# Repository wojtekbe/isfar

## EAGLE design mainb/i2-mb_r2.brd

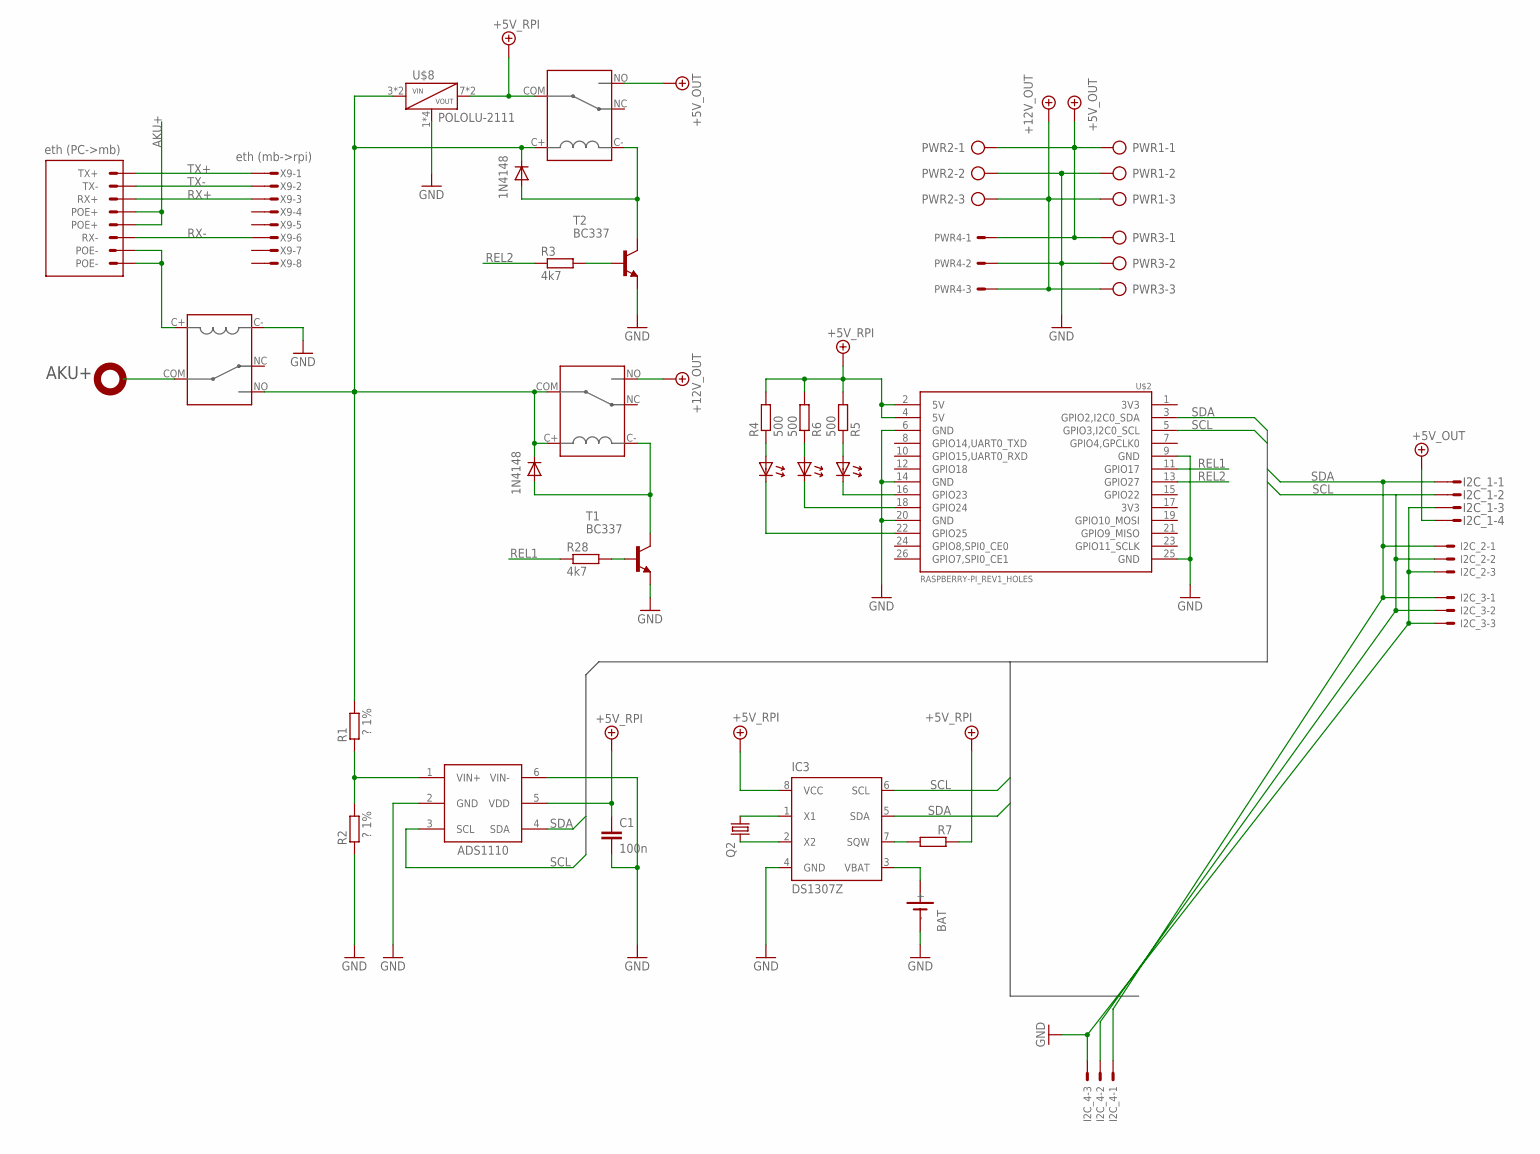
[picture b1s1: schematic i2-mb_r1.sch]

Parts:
BAT: SN2032
C1: 100n; C0603
I2C_1: MICROMATCH-4
I2C_2, I2C_3, I2C_4: C-GRID-03-70553; 70553-03
IC1: ADS1110; SOT-23-6
IC3: DS1307Z; SOIC8
LED1, LED2, LED3: LED0603; D0603
PWR1, PWR2, PWR3: TBMP5103RC-KFV1; TBMP5103RC-KF
PWR4: C-GRID-03-70543; 70543-03
Q2: CRYSTAL; CFPX-217
R1, R2: ? 1%; R0603
R3, R28: 4k7; R0603
R4, R5, R6: 500; R0603
R7: R-EU_R0603; R0603
T1, T2: BC337; TO92
U$2: RASPBERRY-PI_REV1_HOLES; RASPBERRY-PI_HOLES
U$3, U$4: 1N4148; D0603
U$5, U$6, U$7: FBR51; PC_RELAY
U$8: POLOLU-2111
X9: eth (mb->rpi); MICROMATCH-8
X_ETH: eth (PC->mb); 8P8C-TOP

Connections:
+5V: I2C_1.4, PWR1.1, PWR2.1, PWR3.1, PWR4.1, U$5.NO
+12V_IN: R1.1, U$3.2 (C), U$4.2 (C), U$5.C+, U$6.NO, U$7.C+, U$7.COM, U$8.3 (VIN), U$8.4 (VIN)
+12V_OUT: PWR1.3, PWR2.3, PWR3.3, PWR4.3, U$7.NO
AKU+: U$6.COM, X_ETH.4 (POE+), X_ETH.5 (POE+)
GND: BAT.-, C1.2, I2C_1.3, I2C_2.3, I2C_3.3, I2C_4.3, IC1.2 (GND), IC1.6 (VIN-), IC3.4 (GND), PWR1.2, PWR2.2, PWR3.2, PWR4.2, R2.2, T1.1 (E), T2.1 (E), U$2.6 (GND), U$2.9 (GND), U$2.14 (GND), U$2.20 (GND), U$2.25 (GND), U$6.C-, U$8.1 (GND), U$8.2 (GND), U$8.5 (GND), U$8.6 (GND); also elsewhere on the board
LED2: LED2.2 (C), U$2.16 (GPIO23)
LED3: LED3.2 (C), U$2.18 (GPIO24)
unnamed: R3.2, T2.2 (B)
unnamed: T2.3 (C), U$3.1 (A), U$5.C-
unnamed: BAT.+, IC3.3 (VBAT)
unnamed: LED2.1 (A), R5.1
unnamed: LED1.1 (A), R4.1
unnamed: IC3.1 (X1), Q2.1
unnamed: LED1.2 (C), U$2.22 (GPIO25)
unnamed: LED3.1 (A), R6.1
unnamed: IC3.2 (X2), Q2.2
unnamed: IC3.7 (SQW), R7.2
unnamed: T1.3 (C), U$4.1 (A), U$7.C-
unnamed: R28.2, T1.2 (B)
POE-: U$6.C+, X_ETH.7 (POE-), X_ETH.8 (POE-)
REL1: R28.1, U$2.11 (GPIO17)
REL2: R3.1, U$2.13 (GPIO27)
RX-: X9.6, X_ETH.6 (RX-)
SCL: I2C_1.2, I2C_2.2, I2C_3.2, I2C_4.2, IC1.3 (SCL), IC3.6 (SCL), U$2.5 (GPIO3,I2C0_SCL)
SDA: I2C_1.1, I2C_2.1, I2C_3.1, I2C_4.1, IC1.4 (SDA), IC3.5 (SDA), U$2.3 (GPIO2,I2C0_SDA)
TX+: X9.1, X_ETH.1 (TX+)
V_SENS: IC1.1 (VIN+), R1.2, R2.1

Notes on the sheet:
AKU+

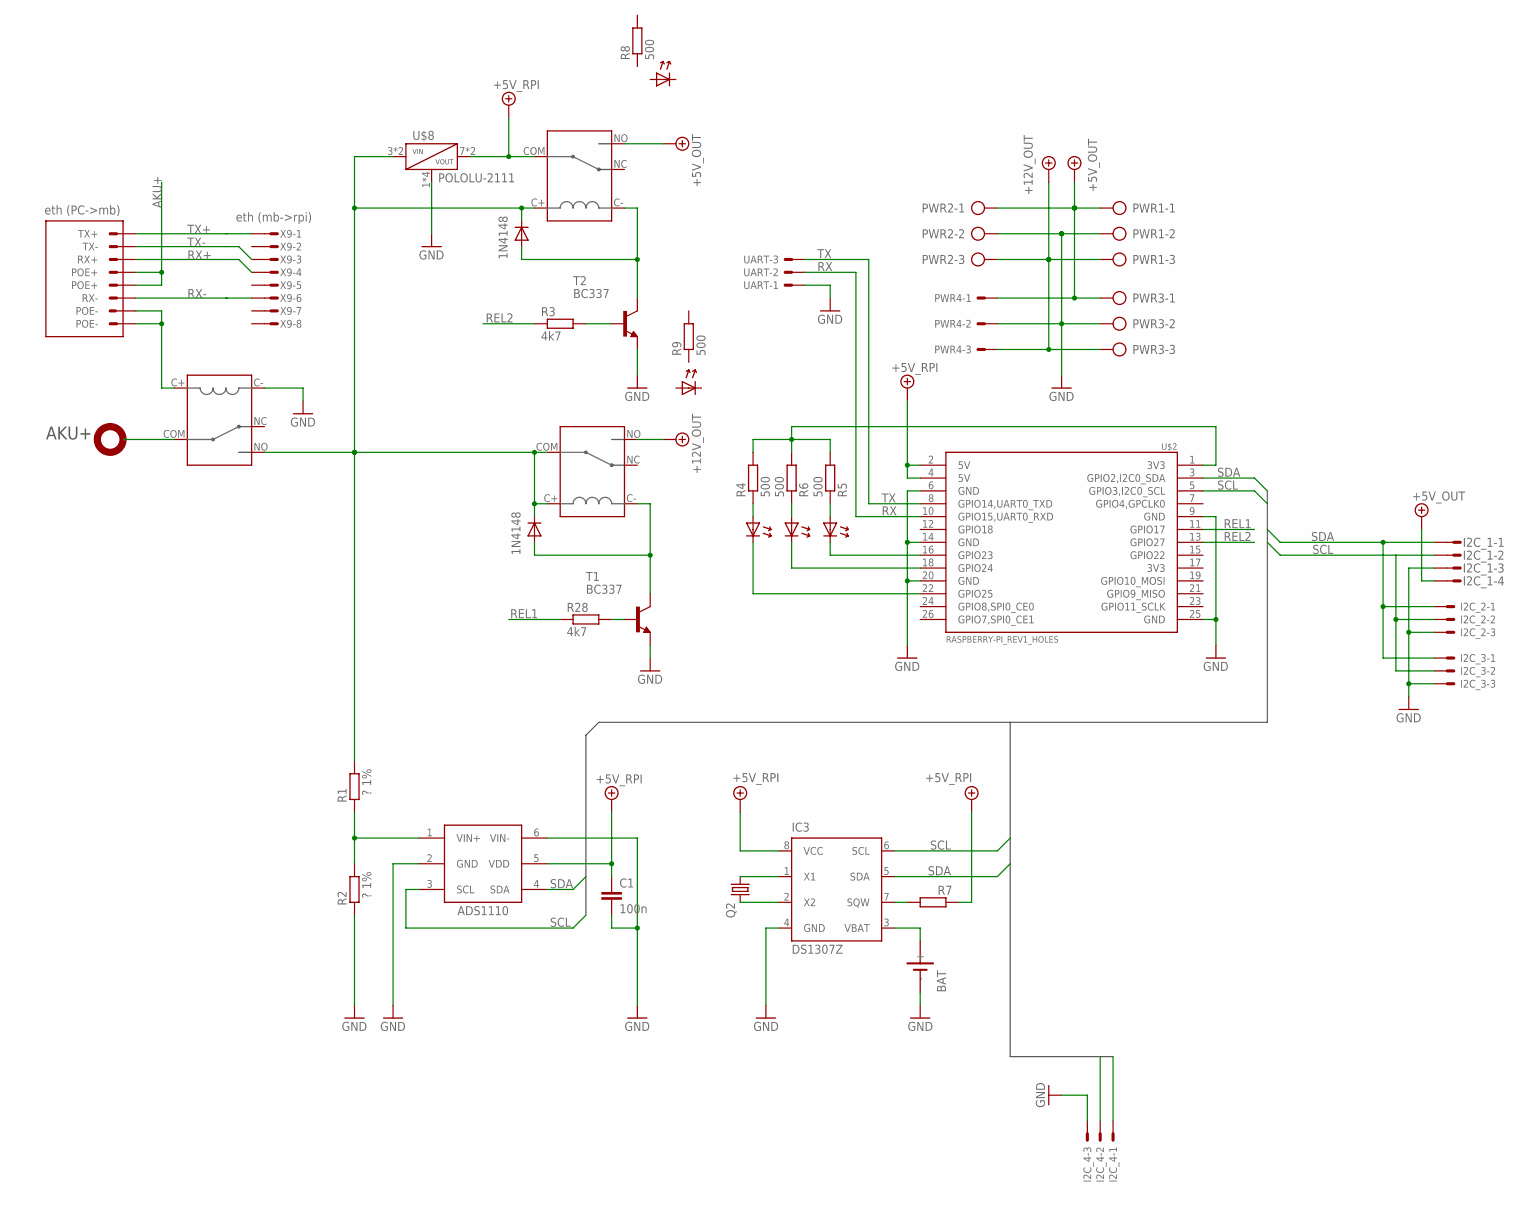
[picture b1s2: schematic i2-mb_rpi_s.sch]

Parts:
BAT: SN2032
C1: 100n; C0603
I2C_1: MICROMATCH-4
I2C_2, I2C_3, I2C_4: C-GRID-03-70553; 70553-03
IC1: ADS1110; SOT-23-6
IC3: DS1307Z; SOIC8
LED1, LED2, LED3, LED4, LED5: LED0603; D0603
PWR1, PWR2, PWR3: TBMP5103RC-KFV1; TBMP5103RC-KF
PWR4: C-GRID-03-70543; 70543-03
Q2: CRYSTAL; CFPX-217
R1, R2: ? 1%; R0603
R3, R28: 4k7; R0603
R4, R5, R6, R8, R9: 500; R0603
R7: R-EU_R0603; R0603
T1, T2: BC337; TO92
U$2: RASPBERRY-PI_REV1_HOLES; RASPBERRY-PI_HOLES
U$3, U$4: 1N4148; D0603
U$5, U$6, U$7: FBR51; PC_RELAY
U$8: POLOLU-2111
UART: C-GRID-03-70543; 70543-03
X9: eth (mb->rpi); MICROMATCH-8
X_ETH: eth (PC->mb); 8P8C-TOP

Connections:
+5V: I2C_1.4, PWR1.1, PWR2.1, PWR3.1, PWR4.1, U$5.NO
+12V_IN: R1.1, U$3.2 (C), U$4.2 (C), U$5.C+, U$6.NO, U$7.C+, U$7.COM, U$8.3 (VIN), U$8.4 (VIN)
+12V_OUT: PWR1.3, PWR2.3, PWR3.3, PWR4.3, U$7.NO
AKU+: U$6.COM, X_ETH.4 (POE+), X_ETH.5 (POE+)
GND: BAT.-, C1.2, I2C_1.3, I2C_2.3, I2C_3.3, I2C_4.3, IC1.2 (GND), IC1.6 (VIN-), IC3.4 (GND), PWR1.2, PWR2.2, PWR3.2, PWR4.2, R2.2, T1.1 (E), T2.1 (E), U$2.6 (GND), U$2.9 (GND), U$2.14 (GND), U$2.20 (GND), U$2.25 (GND), U$6.C-, U$8.1 (GND), U$8.2 (GND), U$8.5 (GND), U$8.6 (GND), UART.1
LED2: LED2.2 (C), U$2.16 (GPIO23)
LED3: LED3.2 (C), U$2.18 (GPIO24)
unnamed: R3.2, T2.2 (B)
unnamed: T2.3 (C), U$3.1 (A), U$5.C-
unnamed: BAT.+, IC3.3 (VBAT)
unnamed: LED2.1 (A), R5.1
unnamed: LED1.1 (A), R4.1
unnamed: IC3.1 (X1), Q2.1
unnamed: LED1.2 (C), U$2.22 (GPIO25)
unnamed: LED3.1 (A), R6.1
unnamed: IC3.2 (X2), Q2.2
unnamed: IC3.7 (SQW), R7.2
unnamed: T1.3 (C), U$4.1 (A), U$7.C-
unnamed: R28.2, T1.2 (B)
POE-: U$6.C+, X_ETH.7 (POE-), X_ETH.8 (POE-)
REL1: R28.1, U$2.11 (GPIO17)
REL2: R3.1, U$2.13 (GPIO27)
RX: U$2.10 (GPIO15,UART0_RXD), UART.2
RX-: X9.6, X_ETH.6 (RX-)
SCL: I2C_1.2, I2C_2.2, I2C_3.2, I2C_4.2, IC1.3 (SCL), IC3.6 (SCL), U$2.5 (GPIO3,I2C0_SCL)
SDA: I2C_1.1, I2C_2.1, I2C_3.1, I2C_4.1, IC1.4 (SDA), IC3.5 (SDA), U$2.3 (GPIO2,I2C0_SDA)
TX: U$2.8 (GPIO14,UART0_TXD), UART.3
TX+: X9.1, X_ETH.1 (TX+)
V_SENS: IC1.1 (VIN+), R1.2, R2.1

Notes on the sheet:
AKU+

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
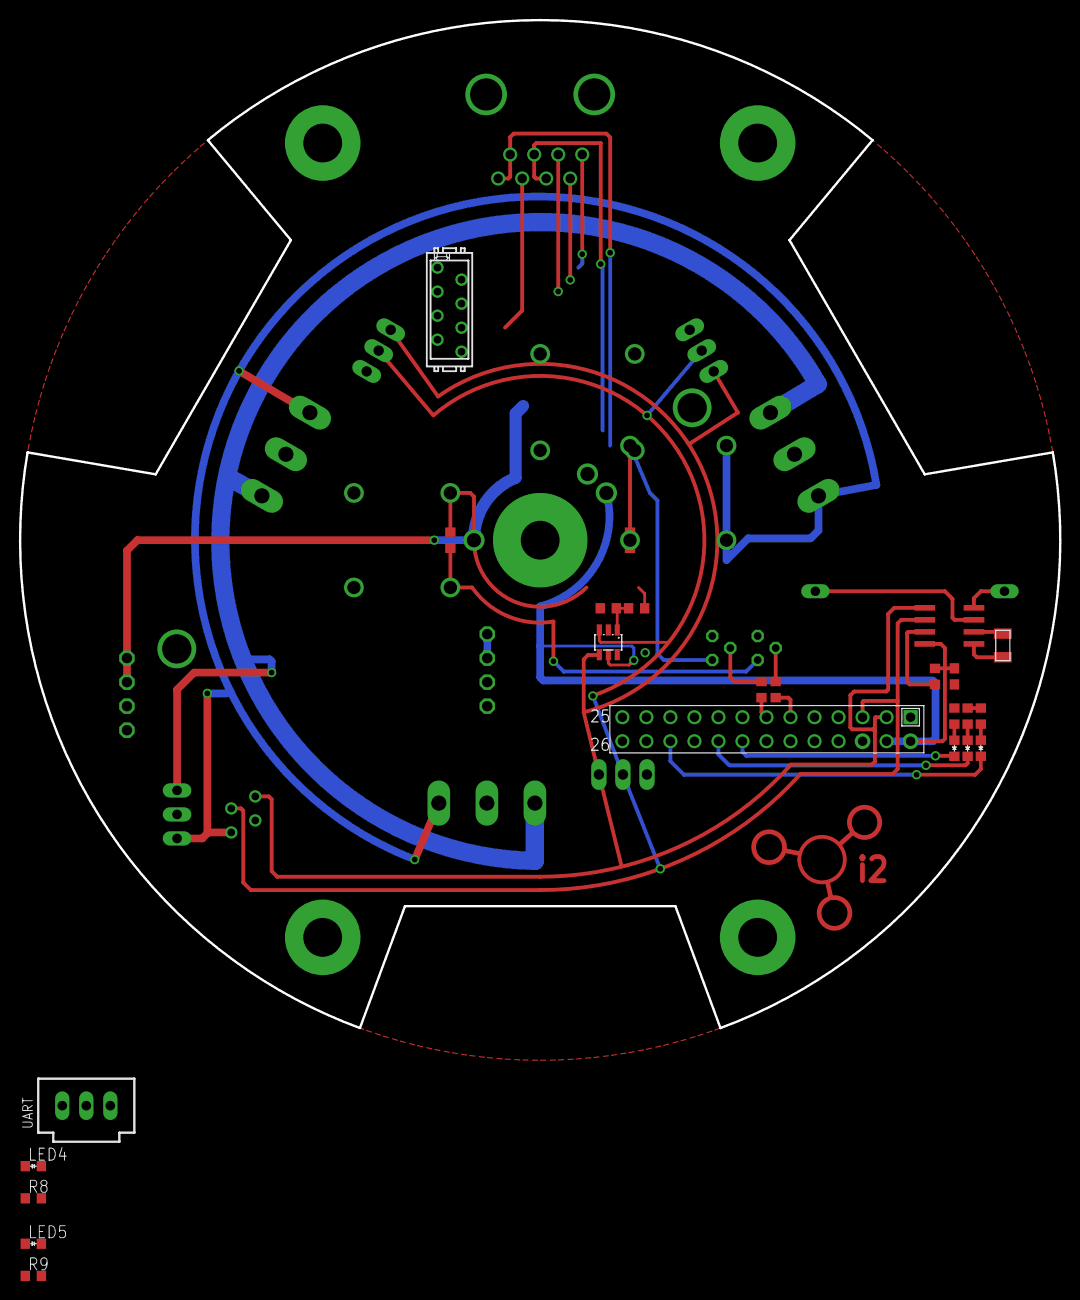
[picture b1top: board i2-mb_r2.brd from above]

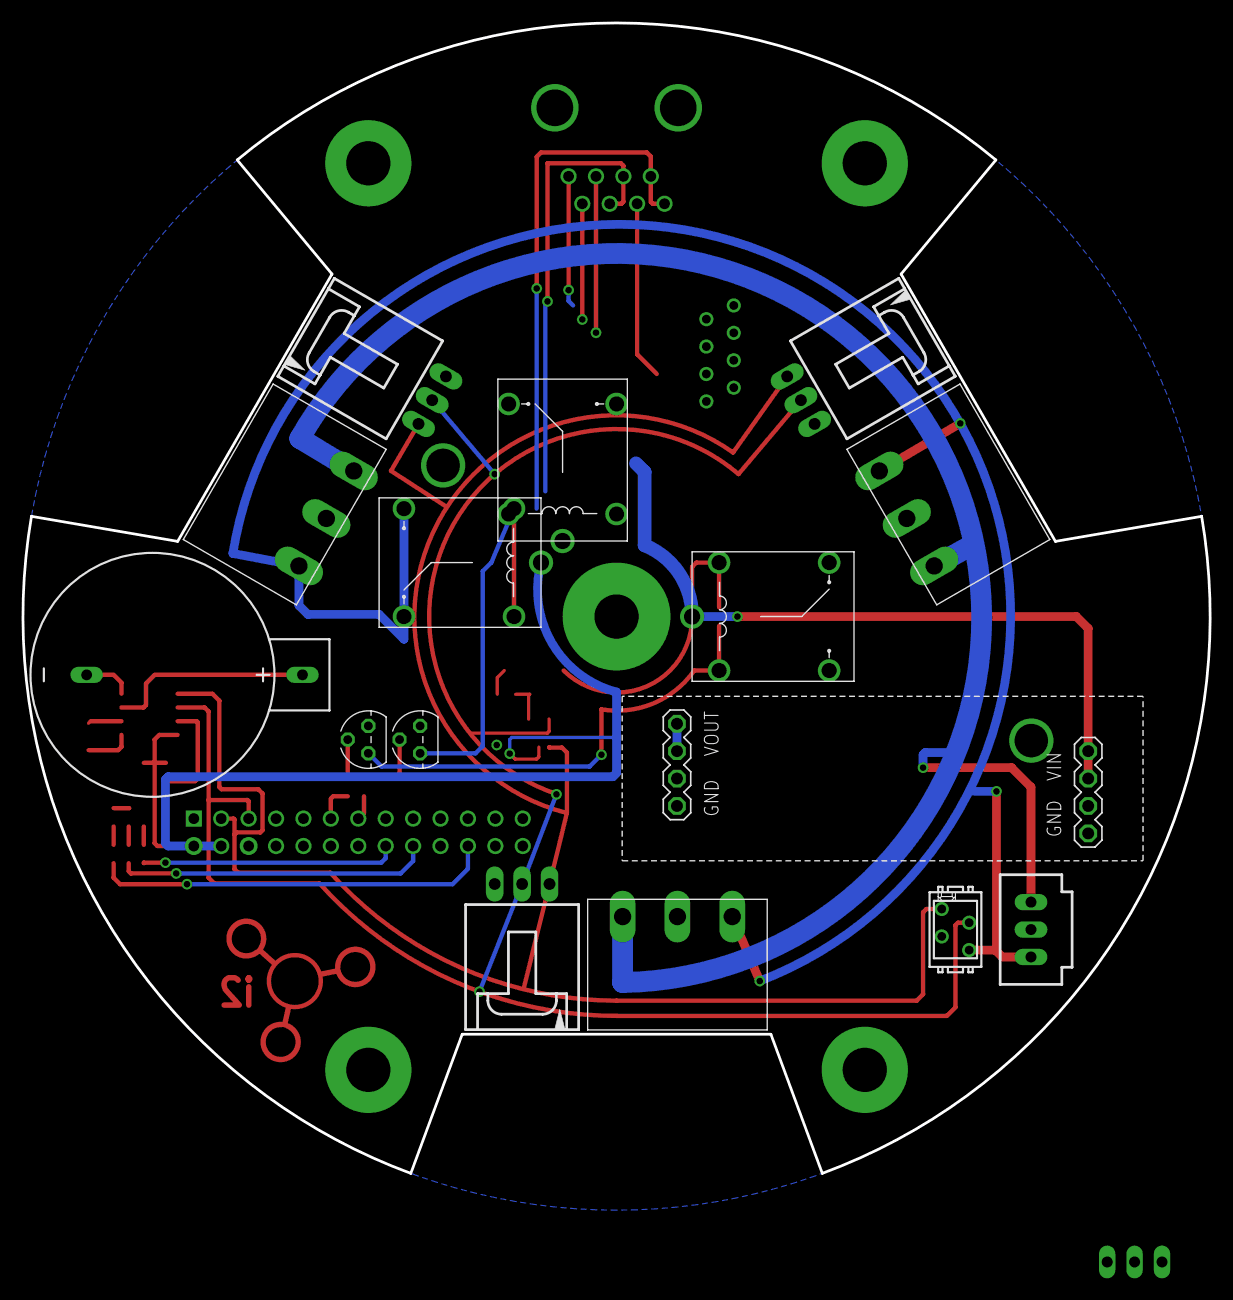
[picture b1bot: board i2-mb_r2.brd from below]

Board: 2 copper layers, 110.0 x 106.6 mm, 41 parts (15 on the bottom side), 33 nets.

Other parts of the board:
U$1: I2-LOGO
